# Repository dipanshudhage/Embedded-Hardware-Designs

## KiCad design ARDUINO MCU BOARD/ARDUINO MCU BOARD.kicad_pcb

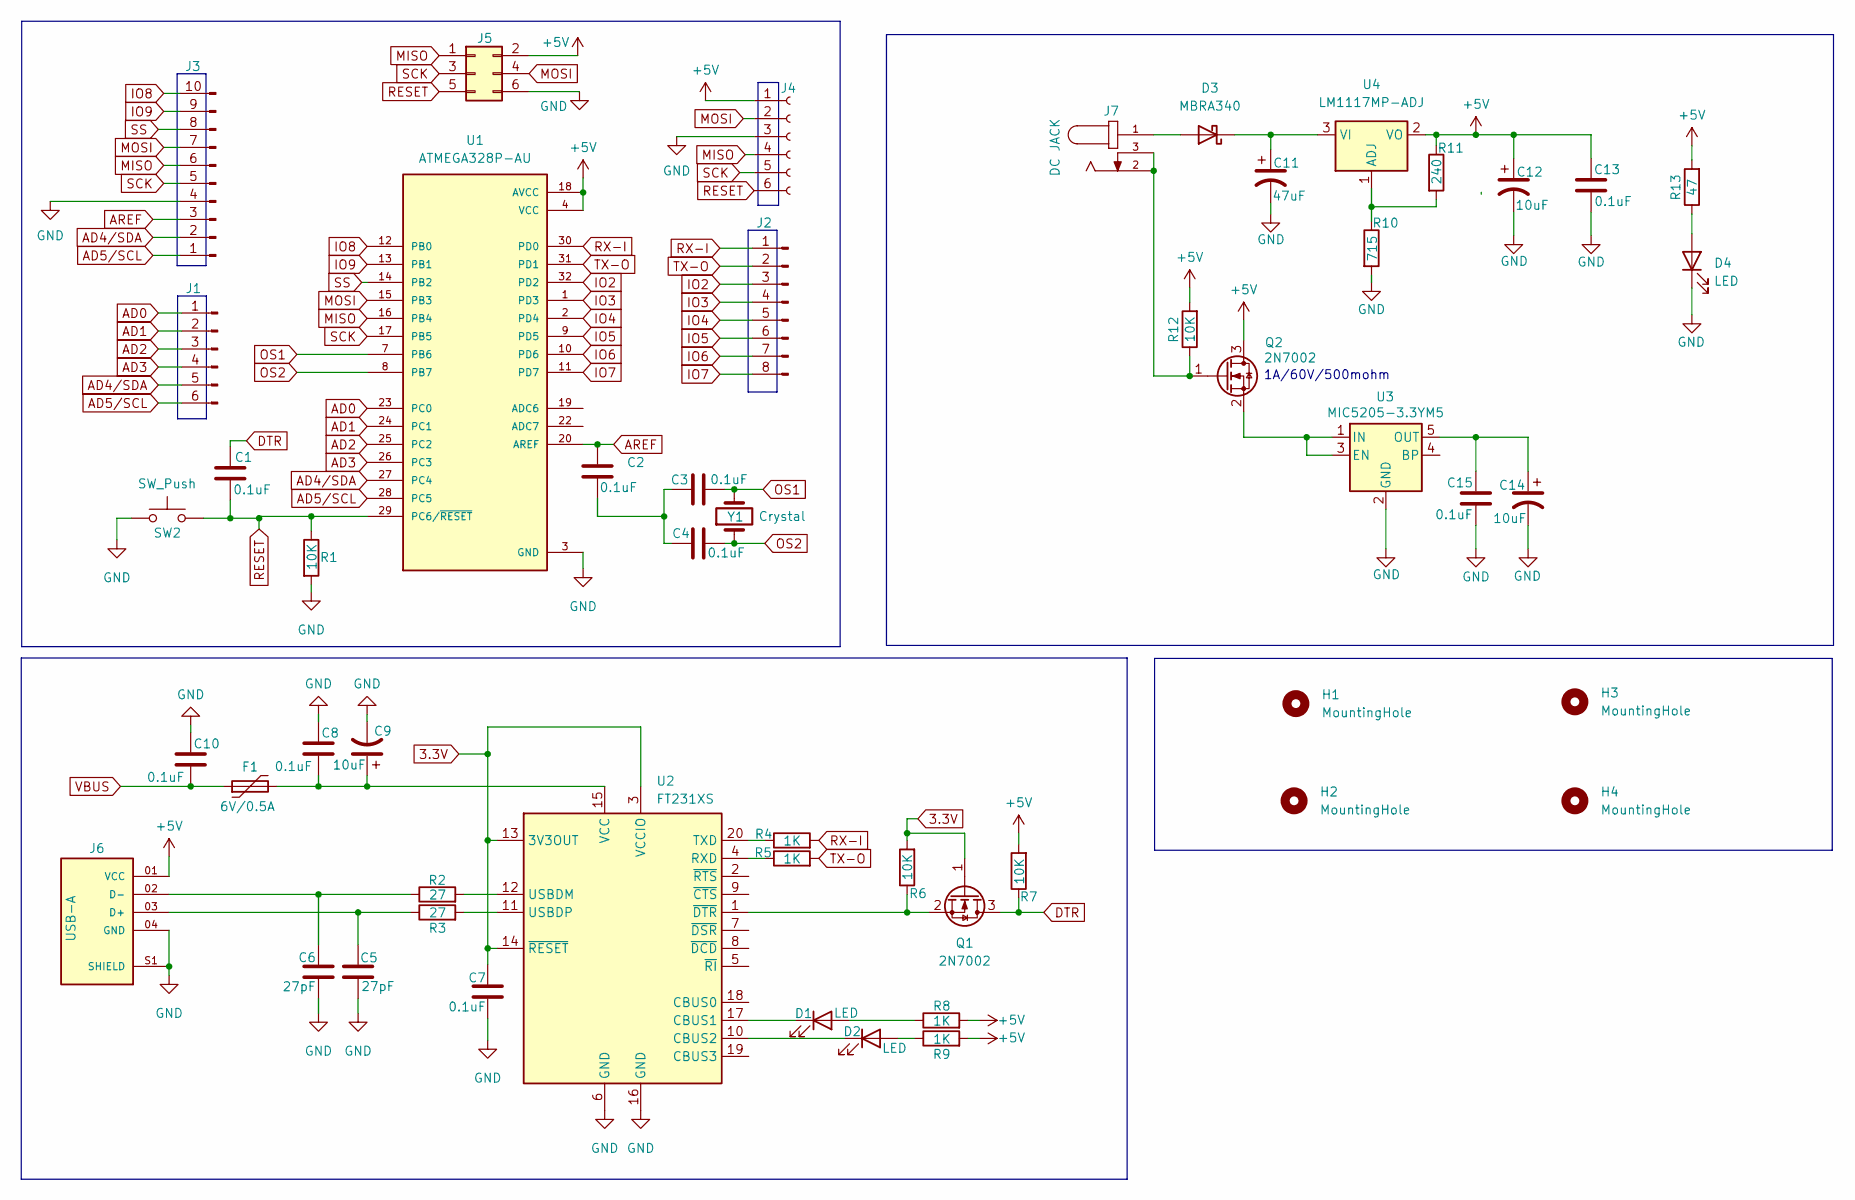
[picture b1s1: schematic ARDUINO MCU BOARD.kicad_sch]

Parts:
C1, C2, C3, C4, C7, C8, C10, C13, C15: 0.1uF; C_0805_2012Metric
C5, C6: 27pF; C_0805_2012Metric
C9: 10uF; C_0805_2012Metric
C11: 47uF; CP_EIA-3216-18_Kemet-A
C12, C14: 10uF; CP_EIA-3216-18_Kemet-A
D1, D2, D4: LED; LED_0805_2012Metric
D3: MBRA340; D_SMA
F1: 6V/0.5A; Fuse_1206_3216Metric
H1, H2, H3, H4: MountingHole; MountingHole_3.2mm_M3
J1: Conn_01x06_Pin; PinSocket_1x06_P2.54mm_Vertical
J2: Conn_01x08_Pin; PinSocket_1x08_P2.54mm_Vertical
J3: Conn_01x10_Pin; PinSocket_1x10_P2.54mm_Vertical
J4: Conn_01x06_Socket; PinSocket_1x06_P2.54mm_Vertical
J5: Conn_02x03_Odd_Even; PinHeader_2x03_P2.54mm_Vertical
J6: USB-A; SAMTEC_USB-A-S-S-B-TH; MPN USB-A-S-S-B-TH
J7: DC JACK; GCT_DCJ200-10-A-XX-K_REVA; PARTREV A
Q1, Q2: 2N7002; SOT-23
R1, R6, R7, R12: 10K; R_0805_2012Metric
R2, R3: 27; R_0805_2012Metric
R4, R5, R8, R9: 1K; R_0805_2012Metric
R10: 715; R_0805_2012Metric
R11: 240; R_0805_2012Metric
R13: 47; R_0805_2012Metric
SW2: SW_Push; SW_Push_1P1T_NO_CK_KMR2
U1: ATMEGA328P-AU; QFP80P900X900X120-32N; PARTREV 8271A
U2: FT231XS; SSOP-20_3.9x8.7mm_P0.635mm
U3: MIC5205-3.3YM5; SOT-23-5
U4: LM1117MP-ADJ; SOT-223-3_TabPin2
Y1: Crystal; XTAL_ABM3-8.000MHZ-D2Y-T

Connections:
3.3V: C7.1, Q1.1 (G), R6.2, U2.3 (VCCIO), U2.13 (3V3OUT), U2.14 (~RESET)
+5V: C12.1, C13.1, J4.1, J5.2, J6.01 (VCC), Q2.3 (D), R7.2, R8.2, R9.2, R11.1, R12.2, R13.2, U1.4 (VCC), U1.6 (VCC), U1.18 (AVCC), U4.2 (VO)
AD0: J1.1, U1.23 (PC0)
AD1: J1.2, U1.24 (PC1)
AD2: J1.3, U1.25 (PC2)
AD3: J1.4, U1.26 (PC3)
AD4/SDA: J1.5, J3.2, U1.27 (PC4)
AD5/SCL: J1.6, J3.1, U1.28 (PC5)
AREF: C2.1, J3.3, U1.20 (AREF)
DTR: C1.2, Q1.3 (D), R7.1
GND: C5.2, C6.2, C7.2, C8.1, C9.2, C10.1, C11.2, C12.2, C13.2, C14.2, C15.2, D4.1 (K), J3.4, J4.3, J5.6, J6.04 (GND), J6.S1 (SHIELD), J6.S2 (SHIELD), R1.2, R10.2, SW2.1, U1.3 (GND), U1.5 (GND), U1.21 (GND), U2.6 (GND), U2.16 (GND), U3.2 (GND)
IO2: J2.3, U1.32 (PD2)
IO3: J2.4, U1.1 (PD3)
IO4: J2.5, U1.2 (PD4)
IO5: J2.6, U1.9 (PD5)
IO6: J2.7, U1.10 (PD6)
IO7: J2.8, U1.11 (PD7)
IO8: J3.10, U1.12 (PB0)
IO9: J3.9, U1.13 (PB1)
MISO: J3.6, J4.4, J5.1, U1.16 (PB4)
MOSI: J3.7, J4.2, J5.4, U1.15 (PB3)
unnamed: C2.2, C3.1, C4.1
unnamed: D1.2 (A), R8.1
unnamed: D1.1 (K), U2.17 (CBUS1)
unnamed: D2.2 (A), R9.1
unnamed: D2.1 (K), U2.10 (CBUS2)
unnamed: D3.2 (A), J7.1
unnamed: C11.1, D3.1 (K), U4.3 (VI)
unnamed: D4.2 (A), R13.1
unnamed: C5.1, J6.03 (D+), R3.1
unnamed: C6.1, J6.02 (D-), R2.1
unnamed: Q1.2 (S), R6.1, U2.1 (~DTR)
unnamed: J7.2, J7.3, Q2.1 (G), R12.1
unnamed: Q2.2 (S), U3.1 (IN), U3.3 (EN)
unnamed: R5.1, U2.4 (RXD)
unnamed: R4.1, U2.20 (TXD)
unnamed: R2.2, U2.12 (USBDM)
unnamed: R3.2, U2.11 (USBDP)
unnamed: C8.2, C9.1, F1.2, U2.15 (VCC)
unnamed: C14.1, C15.1, U3.5 (OUT)
unnamed: R10.1, R11.2, U4.1 (ADJ)
OS1: C3.2, U1.7 (PB6), Y1.2
OS2: C4.2, U1.8 (PB7), Y1.1
RESET: C1.1, J4.6, J5.5, R1.1, SW2.2, U1.29 (PC6/~RESET)
RX-I: J2.1, R4.2, U1.30 (PD0)
SCK: J3.5, J4.5, J5.3, U1.17 (PB5)
SS: J3.8, U1.14 (PB2)
TX-O: J2.2, R5.2, U1.31 (PD1)
VBUS: C10.2, F1.1

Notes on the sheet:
1A/60V/500mohm

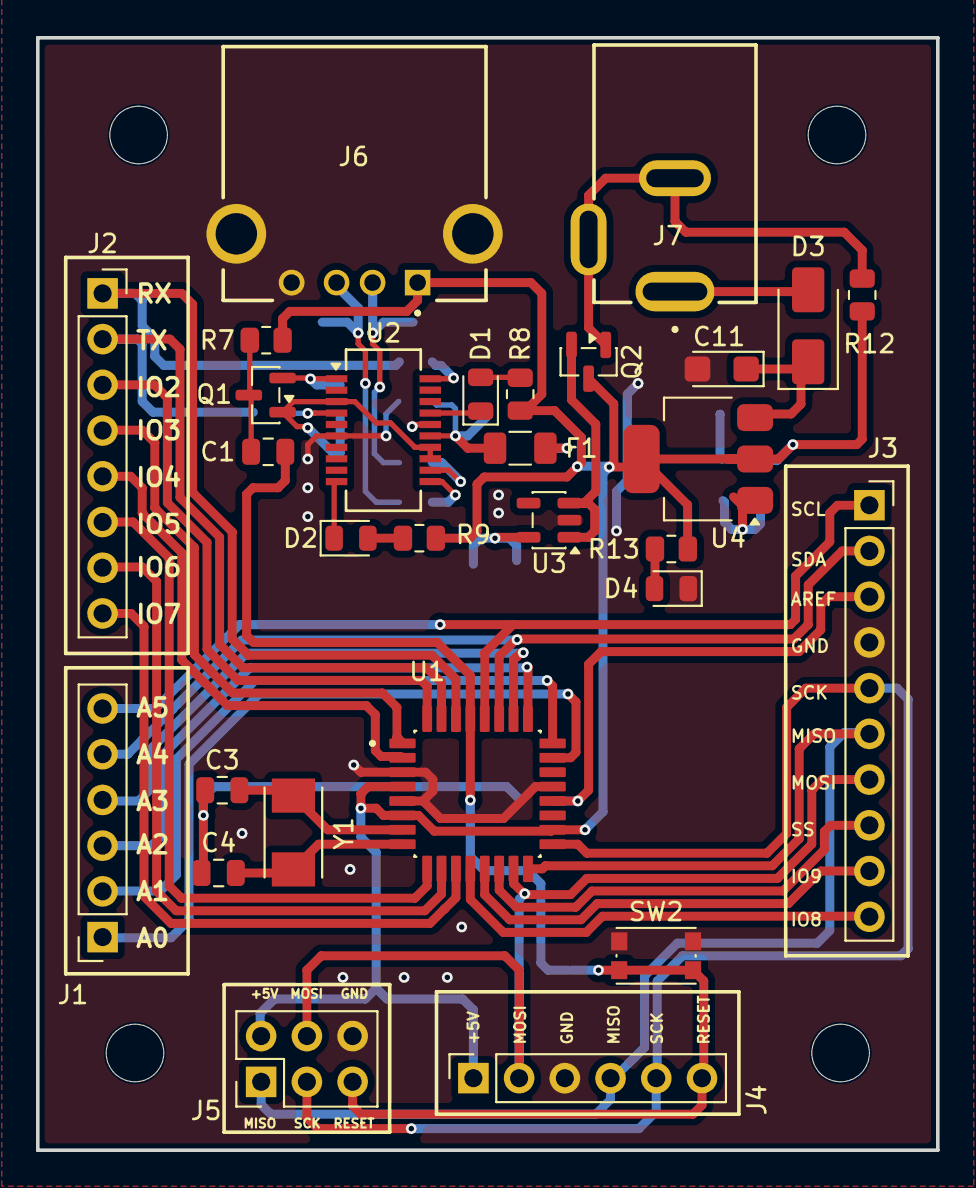
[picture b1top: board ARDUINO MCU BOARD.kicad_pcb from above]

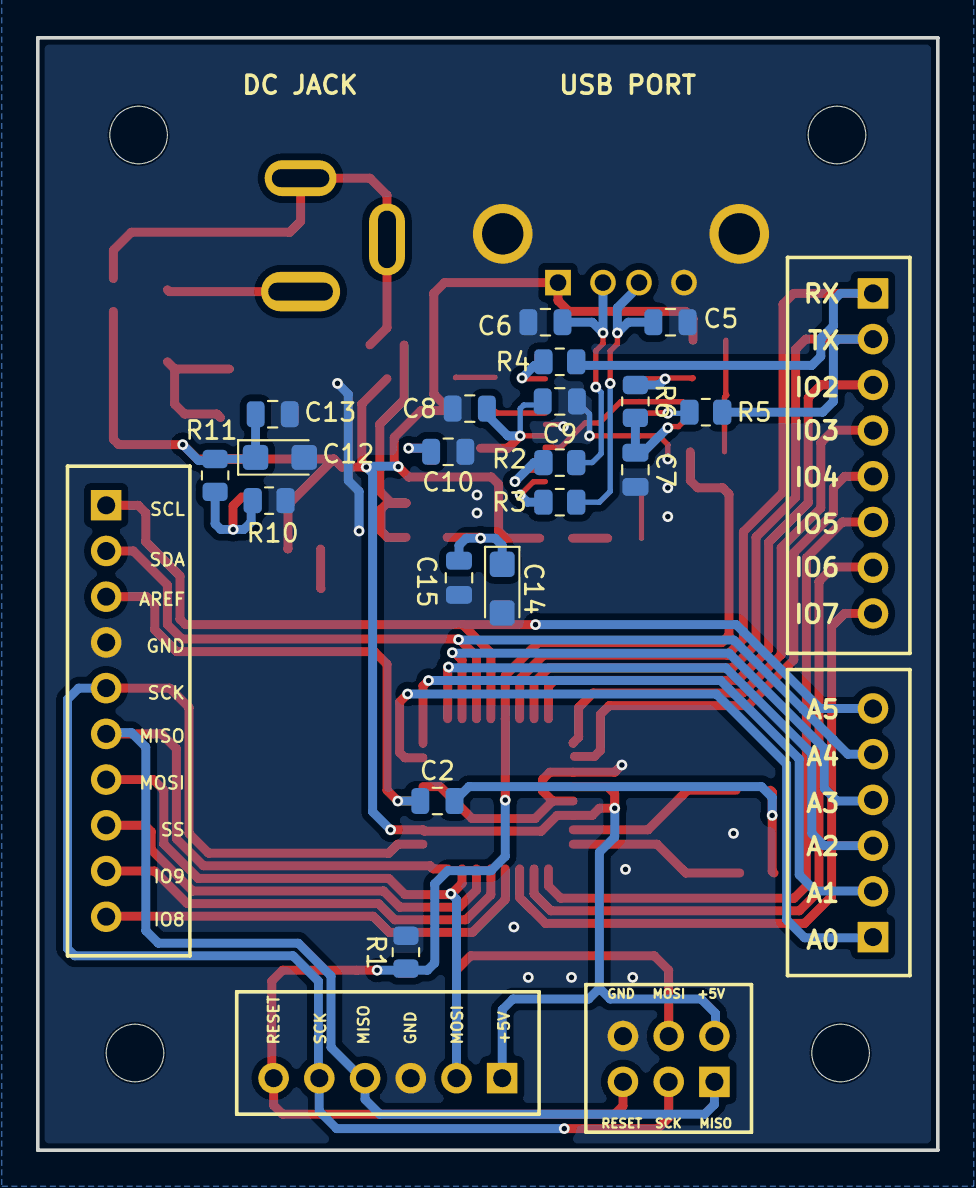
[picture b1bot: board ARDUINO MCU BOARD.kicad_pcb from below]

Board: 2 copper layers, 50.0 x 61.8 mm, 52 parts (19 on the bottom side), 49 nets.
